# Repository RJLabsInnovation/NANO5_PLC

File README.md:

NANO5_PLC
===========
  Design and (C) 2021 RJLabs Innovation <rjlabs.innovation@gmail.com> 
  
  Provided under the terms of the CC0 1.0 Universal license.

Overview
--------
  This design board is based Outseal PLC V.5 [Outseal Website](http://www.outseal.com/web/produk). The main goal of this project to provide sigle side PCB that can be produce in house using transfer paper or negatif film method.

Key Feature
-------- 
* 2 Analog Input 0 - 20mA Or 0 -5V
* Built-in Modbus RTU
* Built-in external EEPROM 24CXX
* 8 Isolated Digital Input (12V - 24V)
* 2 Relay On Board with Surge Protection
* 6 Open Colector Digital Output
* Add On RTC DS3231 & Bluethoot HC05/06 

TODO
--------
* Add Regulator input power From LDO using Switching fore wide input voltage
* Add filter On input power stage
*

FINAL PRODUCT 3D RENDER
--------

Donations
--------
To support this project, you can make a donation to its current maintainer:

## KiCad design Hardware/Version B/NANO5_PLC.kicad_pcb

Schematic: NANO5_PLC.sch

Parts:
C1, C6, C9, C10, C11, C12, C13, C14, C15, C16, C17, C21, C22, C23: C_Small; C_Disc_D3.8mm_W2.6mm_P2.50mm
C5: 100u; CP_Radial_D5.0mm_P2.50mm
C7: 10n; C_0805_2012Metric_Pad1.15x1.40mm_HandSolder
C8, C25, C26, C27: 100n; C_0805_2012Metric
C28, C29: 22p; C_0805_2012Metric
D1: 1N4007; D_SMB
D2, D19: TS4148; D_0805_2012Metric
D3: 1N4007; D_1206_3216Metric
D4, D5, D6, D7, D8, D9, D10, D11, D14, D16, D18, D20: LED; LED_0805_2012Metric
D12: LED_ALT; LED_D3.0mm
D13: Grn; LED_0805_2012Metric_Pad1.15x1.40mm_HandSolder
D15, D17, D21: TS4148; D_1206_3216Metric
F1: Polyfuse_Small; Fuse_1206_3216Metric
FID1, FID2: Fiducial; Fiducial_1mm_Mask2mm
H1, H2, H3, H4: MountingHole; MountingHole_3.2mm_M3_DIN965_Pad
H5, H6, H7: MountingHole; mouse-bite-2mm-slot
J2, J3, J4, J5, J6, J16, J17, J18, J19, J20: Conn_01x03; TerminalBlock_bornier-3_P5.08mm
J7, J10: Conn_01x06; PinHeader_1x06_P2.54mm_Vertical
J8, J12, J21: Conn_01x02; PinHeader_1x02_P2.54mm_Vertical
J9: Conn_02x04_Odd_Even; PinSocket_2x04_P2.54mm_Vertical
J11: Debug; PinHeader_1x06_P2.54mm_Vertical
J13: Conn_01x05; PinHeader_1x05_P2.54mm_Vertical
J22: MP1584; SRT_MPT1584EN_Module
J23: Conn_01x04; JST_XH_B4B-XH-AM_1x04_P2.50mm_Vertical
J24: Conn_01x02; TerminalBlock_bornier-2_P5.08mm
J25: Conn_02x04_Odd_Even; PinSocket_2x04_P2.54mm_Horizontal
J26: Conn_02x04_Odd_Even; PinHeader_2x04_P2.54mm_Horizontal
K1, K2, K3, K4: SANYOU_SRD_Form_C; Relay_SPDT_SANYOU_SRD_Series_Form_C
Q1, Q2, Q3, Q4, Q5: 2SC1815; SC-59
R1, R2, R3: 1k; R_0805_2012Metric_Pad1.20x1.40mm_HandSolder
R4, R5, R6, R7, R8, R9, R10, R11, R12, R13, R20, R21, R22, R23, R24, R25, R26, R27, R28, R29, R30, R31: R; R_0805_2012Metric_Pad1.20x1.40mm_HandSolder
R14, R15, R16, R17: R_Small; R_0805_2012Metric
R18: 220; R_Axial_DIN0204_L3.6mm_D1.6mm_P5.08mm_Horizontal
R19: 1k; R_0805_2012Metric_Pad1.15x1.40mm_HandSolder
RV1, RV2, RV5, RV6: Varistor; RV_Disc_D12mm_W3.9mm_P7.5mm
RV3, RV4: R_POT; Potentiometer_Bourns_3299W_Vertical
SW1, SW2: SW_DIP_x02; SW_DIP_SPSTx02_Slide_Omron_A6S-210x_W8.9mm_P2.54mm
U2: SP3485EN; SOIC-8_3.9x4.9mm_P1.27mm
U3, U4, U5, U6, U7, U8, U9, U10: EL817; SSO-4_6.7x5.1mm_P2.54mm_Clearance8mm
U11: M24C01; SOIC-8_3.9x4.9mm_P1.27mm
U14: ATmega328-AU; TQFP-32_7x7mm_P0.8mm
U15: LM358; SOIC-8_3.9x4.9mm_P1.27mm
Y1: Crystal_Small; Crystal_SMD_HC49-SD

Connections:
2: U6.4
3: U5.4
4: U4.4
5: U3.4
+5V: C5.1, C6.1, C23.1, C26.1, C27.1, D1.1 (K), D2.1, D15.1, D17.1, D19.1, D21.1, J6.1, J7.5, J10.5, J21.2, J22.3, K1.2, K2.2, K3.2, K4.2, R1.1, R5.2, R21.2, R23.2, R26.2, R27.2, U2.8 (VCC), U11.8 (VCC), U14.4, U14.6, U14.18
/Vin: C17.1, D3.1 (K), J22.1
A: J6.3, U2.6 (A)
A0: U7.4, U14.23
A1: U8.4, U14.24
A2: U9.4, U14.25
A3: U10.4, U14.26
A4: J7.4, U11.5 (SDA), U14.27
A5: J7.3, U11.6 (SCL), U14.28
A6: C21.1, R16.1, U14.19
A7: C22.1, R17.1, U14.22
B: J6.2, U2.7 (B)
D2: U14.32
D3: U14.1
D4: U14.2
D5: U14.9
D6: R22.2, U14.10
D7: U14.11
D8: U14.12
D9: R28.2, U14.13
D10: U14.14
D11: R20.2, U14.15
D12: R24.2, U14.16
D13: R25.2, U14.17
GND: C5.2, C6.2, C7.2, C17.2, C21.2, C22.2, C23.2, C25.2, C26.2, C27.2, C28.2, C29.2, D13.1 (K), J5.1, J7.6, J10.4, J11.1, J18.1, J20.1, J20.2, J22.2, J22.4, Q1.1 (E), Q2.1 (E), Q3.1 (E), Q4.1 (E), Q5.1 (E), R14.2, R15.2, RV3.2, RV3.3, RV4.2, RV4.3, U2.4 (DI), U2.5 (GND), U3.3, U4.3, U5.3, U6.3, U7.3, U8.3, U9.3, U10.3, U11.1 (E0), U11.2 (E1), U11.3 (E2), U11.4 (VSS), U11.7 (~WC), U14.3, U14.5, U14.21
GNDA: C9.1, C10.1, C11.1, C12.1, C13.1, C14.1, C15.1, C16.1, J17.1, U3.2, U4.2, U5.2, U6.2, U7.2, U8.2, U9.2, U10.2
INA1: J18.2, R14.1, R16.2, SW2.4
INA2: J18.3, R15.1, R17.2, SW2.3
unnamed: C1.1, R28.1, R29.2, U15.3
unnamed: C1.2, R29.1, R30.1
unnamed: C8.1, J11.6
unnamed: C9.2, D4.1 (K), U3.1
unnamed: C10.2, D5.1 (K), U4.1
unnamed: C11.2, D6.1 (K), U5.1
unnamed: C12.2, D7.1 (K), U6.1
unnamed: C13.2, D8.1 (K), U7.1
unnamed: C14.2, D9.1 (K), U8.1
unnamed: C15.2, D10.1 (K), U9.1
unnamed: C16.2, D11.1 (K), U10.1
unnamed: C25.1, U14.20
unnamed: D2.2, J11.3
unnamed: D3.2 (A), F1.1
unnamed: D4.2 (A), R6.2
unnamed: D5.2 (A), R7.2
unnamed: D6.2 (A), R8.2
unnamed: D7.2 (A), R9.2
unnamed: D8.2 (A), R10.2
unnamed: D9.2 (A), R11.2
unnamed: D10.2 (A), R12.2
unnamed: D11.2 (A), R13.2
unnamed: D12.2 (A), R18.2
unnamed: D13.2 (A), R19.1
unnamed: D14.1 (K), D15.2, K3.5, Q2.2 (C)
unnamed: D14.2 (A), R21.1
unnamed: D16.1 (K), D17.2, K4.5, Q3.2 (C)
unnamed: D16.2 (A), R23.1
unnamed: D18.1 (K), D19.2, K2.5, Q4.2 (C)
unnamed: D18.2 (A), R26.1
unnamed: D20.1 (K), D21.2, K1.5, Q5.2 (C)
unnamed: D20.2 (A), R27.1
unnamed: J8.2, J10.2
unnamed: J8.1, J10.3
unnamed: J11.4, R3.1
unnamed: J11.5, R2.1
unnamed: K1.1, RV1.1
unnamed: K1.3, RV1.2
unnamed: K2.1, RV2.1
unnamed: K2.3, RV2.2
unnamed: K3.1, RV5.1
unnamed: K3.3, RV5.2
unnamed: K4.1, RV6.1
unnamed: K4.3, RV6.2
unnamed: Q1.2 (C), R5.1, U2.2 (~RE~), U2.3 (DE)
unnamed: Q1.3 (B), R4.1
unnamed: Q2.3 (B), R20.1
unnamed: Q3.3 (B), R22.1
unnamed: Q4.3 (B), R24.1
unnamed: Q5.3 (B), R25.1
unnamed: R30.2, R31.1, U15.6
unnamed: R31.2, U15.7
unnamed: RV3.1, SW2.1
unnamed: RV4.1, SW2.2
unnamed: U15.1, U15.2, U15.5
OR1: J4.1
OR2: J4.2
OR3: J5.3
OR4: J5.2
RESET: C7.1, C8.2, R1.2, U14.29
RL3: J4.3
RL4: J3.1
RL5: J3.2
RL6: J3.3
RL7: J2.1
RL8: J2.2
RX: J12.1, R3.2, U14.30
RX1: J12.2, U2.1 (RO)
S1: J17.2, R10.1
S2: J17.3, R11.1
S3: J19.1, R12.1
S4: J19.2, R13.1
S5: J19.3, R9.1
S6: J16.1, R8.1
S7: J16.2, R7.1
S8: J16.3, R6.1
TX: R2.2, R4.2, U14.31
V: F1.2, J20.3
VRL: J2.3, J21.1
X1: C28.1, U14.7, Y1.1
X2: C29.1, U14.8, Y1.2

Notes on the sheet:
D13 = R1 D12 = R2 D11 = R3 D10 = R8 D9 = R7 D8 = R6 D7 = R5 D6 = R4 D5 = S8* D4 = S7* D3 = S6* D2 = S5* A0 = S1* A1 = S2* A2 = S3* A3 = S4* A4 = SDA A5 = SCL A6 = A1 A7 = A2
INPUT STAGE
OUTPUT STAGE
REGULATOR CIRCUIT
NANO5 PLC OUTSEAL V5 COMPETIBLE
COPYRIGHT RJLabs Innovation @2021 E-mail : rjlabs.innovation@gmail.com

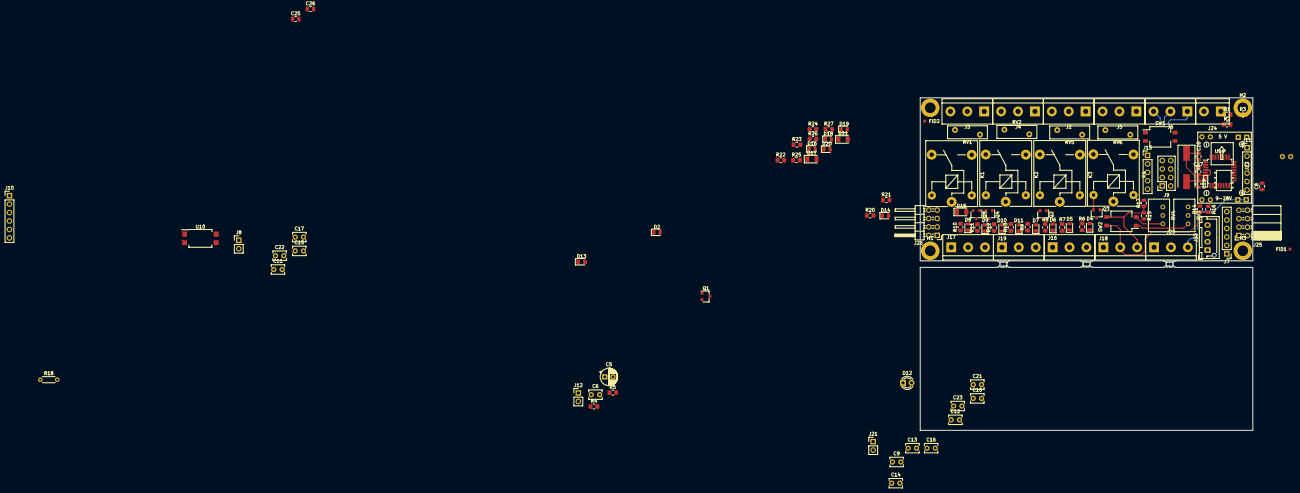
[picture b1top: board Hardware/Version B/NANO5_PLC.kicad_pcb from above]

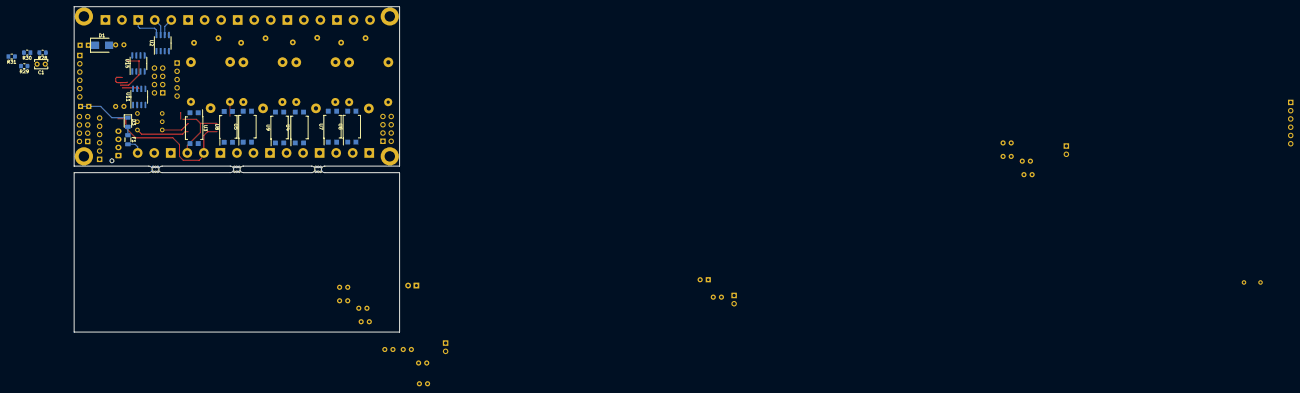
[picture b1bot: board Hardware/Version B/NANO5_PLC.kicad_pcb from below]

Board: 4 copper layers, 100.0 x 100.0 mm, 135 parts (18 on the bottom side), 91 nets.

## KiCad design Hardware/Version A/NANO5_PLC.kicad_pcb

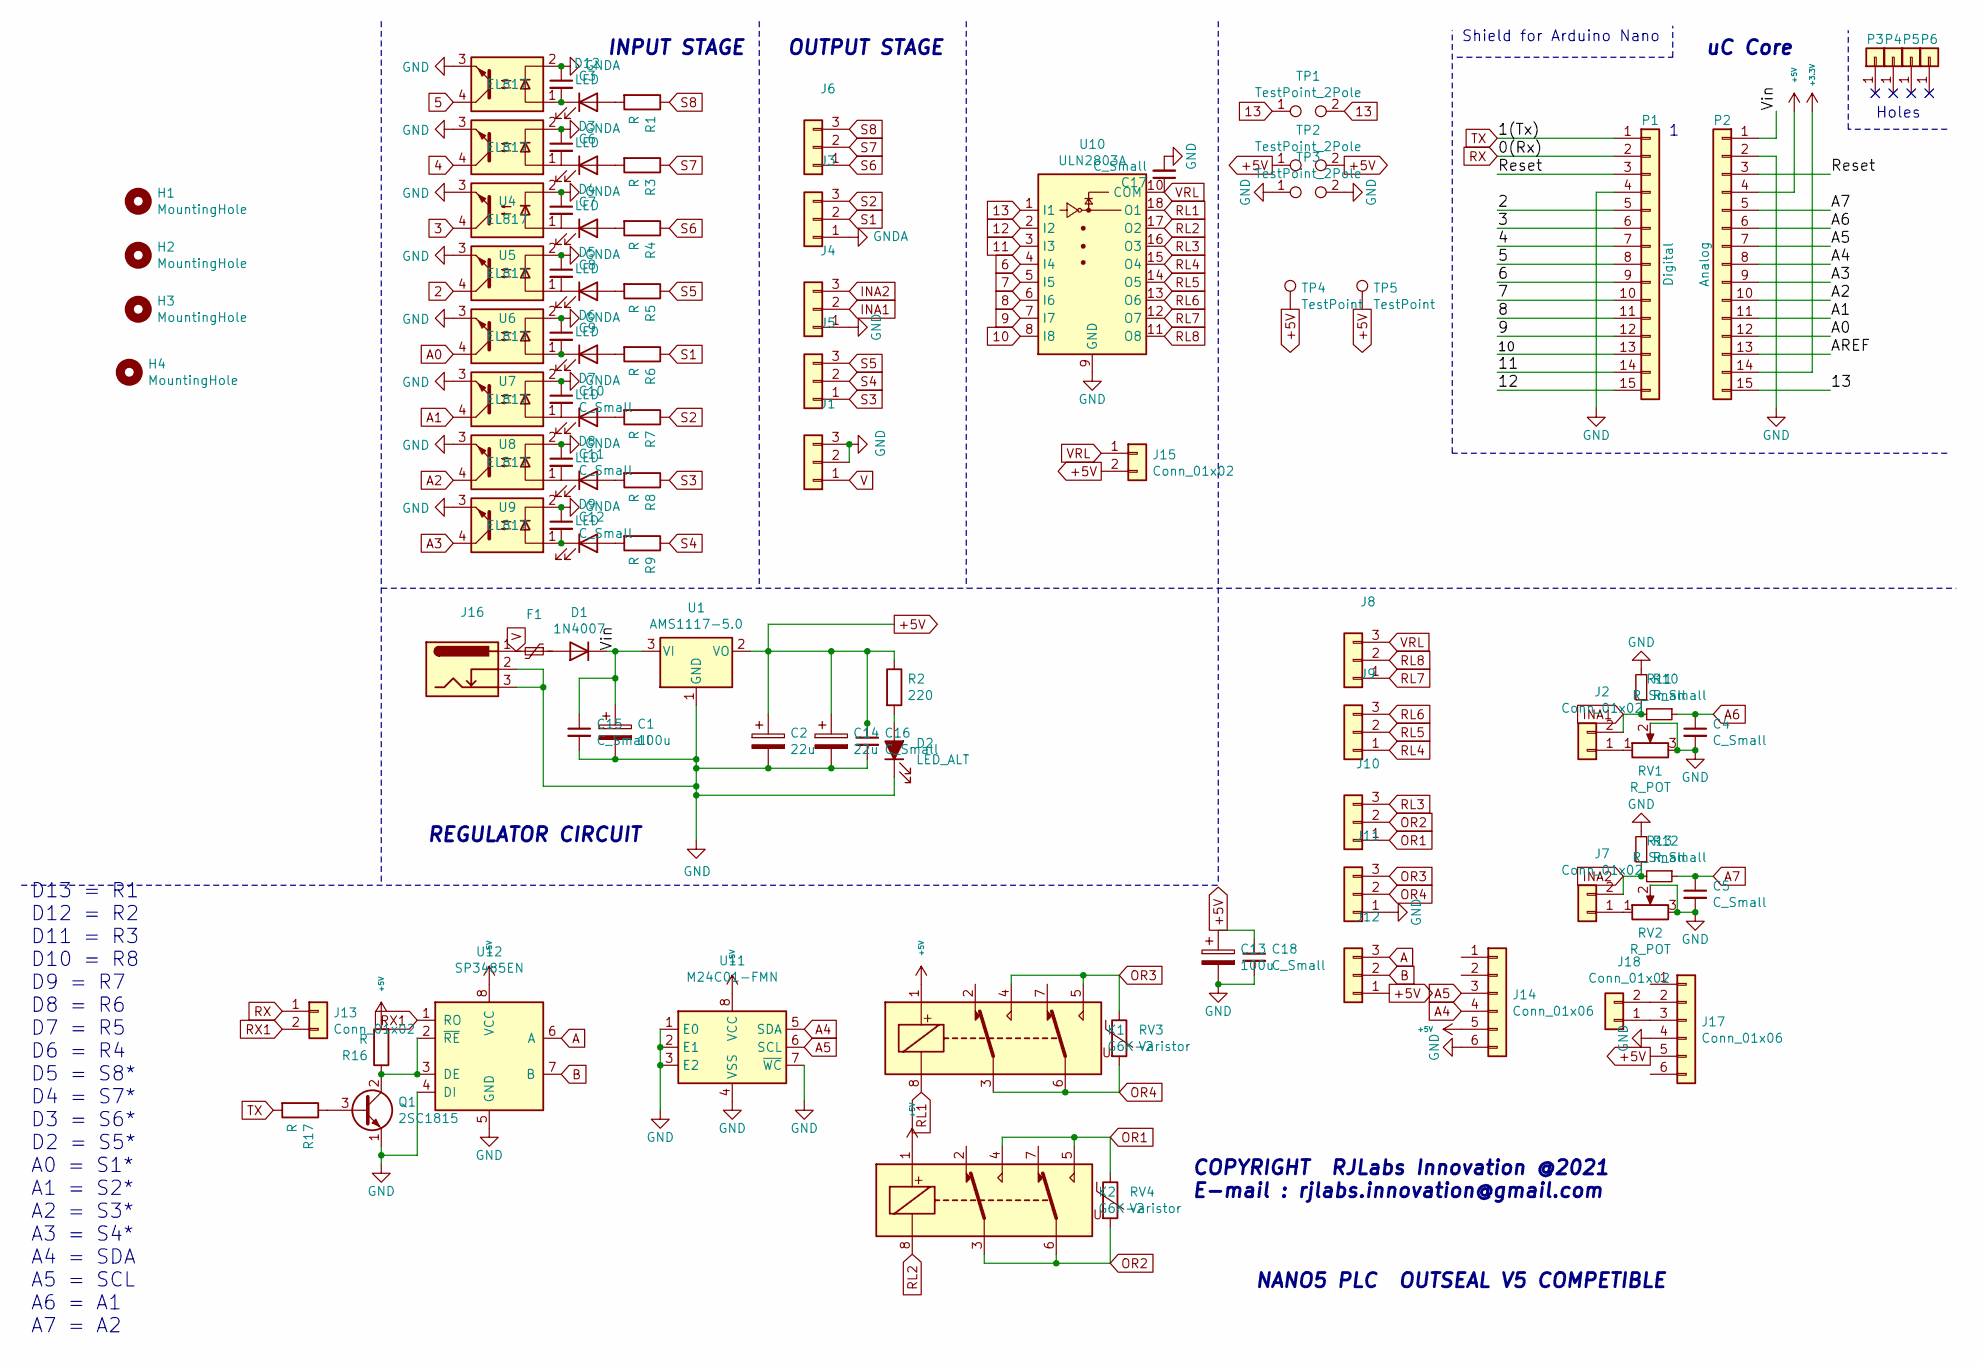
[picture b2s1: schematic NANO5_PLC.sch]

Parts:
C1, C13: 100u; CP_Radial_D5.0mm_P2.50mm
C2, C14: 22u; CP_Radial_D5.0mm_P2.50mm
C3, C4, C5, C6, C7, C8, C9, C10, C11, C12, C15, C16, C17, C18: C_Small; C_Disc_D3.8mm_W2.6mm_P2.50mm
D1: 1N4007; D_A-405_P2.54mm_Vertical_KathodeUp
D2: LED_ALT; LED_D3.0mm
D3, D4, D5, D6, D7, D8, D9, D12: LED; LED_D3.0mm
F1: Polyfuse_Small; Fuse_BelFuse_0ZRE0033FF_L11.4mm_W3.8mm
H1, H2, H3, H4: MountingHole; MountingHole_3.2mm_M3_DIN965_Pad
J1, J3, J4, J5, J6, J8, J9, J10, J11, J12: Conn_01x03; TerminalBlock_Phoenix_MKDS-1,5-3-5.08_1x03_P5.08mm_Horizont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
J2, J7, J13, J15, J18: Conn_01x02; PinHeader_1x02_P2.54mm_Vertical
J14, J17: Conn_01x06; PinHeader_1x06_P2.54mm_Vertical
J16: Barrel_Jack_Switch_Pin3Ring; BarrelJack_Horizontal
K1, K2: G6K-2; Relay_DPDT_Omron_G5V-2
P1: Digital; Socket_Strip_Arduino_1x15
P2: Analog; Socket_Strip_Arduino_1x15
P3, P4, P5, P6: CONN_01X01; 1pin_Nano
Q1: 2SC1815; TO-92_Inline_Wide
R1, R3, R4, R5, R6, R7, R8, R9, R16, R17: R; R_0805_2012Metric_Pad1.20x1.40mm_HandSolder
R2: 220; R_Axial_DIN0204_L3.6mm_D1.6mm_P5.08mm_Horizontal
R10, R11, R12, R13: R_Small; R_Axial_DIN0204_L3.6mm_D1.6mm_P5.08mm_Horizontal
RV1, RV2: R_POT; Potentiometer_Bourns_3299W_Vertical
RV3, RV4: Varistor; RV_Disc_D12mm_W3.9mm_P7.5mm
TP1: TestPoint_2Pole; TestPoint_Bridge_Pitch7.62mm_Drill1.3mm
TP2: TestPoint_2Pole; TestPoint_Bridge_Pitch6.35mm_Drill1.3mm
TP3: TestPoint_2Pole; TestPoint_Bridge_Pitch5.08mm_Drill1.3mm
TP4, TP5: TestPoint; TestPoint_Loop_D1.80mm_Drill1.0mm_Beaded
U1: AMS1117-5.0; SOT-223-3_TabPin2
U2, U3, U4, U5, U6, U7, U8, U9: EL817; DIP-4_W7.62mm
U10: ULN2803A; SOIC-18W_7.5x11.6mm_P1.27mm
U11: M24C01-FMN; SOIC-8_3.9x4.9mm_P1.27mm
U12: SP3485EN; SOIC-8_3.9x4.9mm_P1.27mm

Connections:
2: P1.5, U5.4
3: P1.6, U4.4
4: P1.7, U3.4
5: P1.8, U2.4
6: P1.9, U10.4 (I4)
7: P1.10, U10.5 (I5)
8: P1.11, U10.6 (I6)
9: P1.12, U10.7 (I7)
10: P1.13, U10.8 (I8)
11: P1.14, U10.3 (I3)
12: P1.15, U10.2 (I2)
13: P2.15, TP1.1, TP1.2, U10.1 (I1)
+3V3: P2.14
+5V: C2.1, C13.1, C14.1, C16.1, C18.1, J12.1, J14.5, J15.2, J17.5, K1.1, K2.1, P2.4, R2.1, R16.2, TP2.1, TP2.2, TP4.1, TP5.1, U1.2 (VO), U11.8 (VCC), U12.8 (VCC)
/AREF: P2.13
/Reset: P1.3, P2.3
/Vin: C1.1, C15.1, D1.1 (K), P2.1, U1.3 (VI)
A: J12.3, U12.6 (A)
A0: P2.12, U6.4
A1: P2.11, U7.4
A2: P2.10, U8.4
A3: P2.9, U9.4
A4: J14.4, P2.8, U11.5 (SDA)
A5: J14.3, P2.7, U11.6 (SCL)
A6: C4.1, P2.6, R11.1
A7: C5.1, P2.5, R13.1
B: J12.2, U12.7 (B)
GND: C1.2, C2.2, C4.2, C5.2, C13.2, C14.2, C15.2, C16.2, C17.2, C18.2, D2.1 (K), J1.2, J1.3, J4.1, J11.1, J14.6, J16.2, J16.3, J17.4, P1.4, P2.2, Q1.1 (E), R10.2, R12.2, RV1.2, RV1.3, RV2.2, RV2.3, TP3.1, TP3.2, U1.1 (GND), U2.3, U3.3, U4.3, U5.3, U6.3, U7.3, U8.3, U9.3, U10.9 (GND), U11.1 (E0), U11.2 (E1), U11.3 (E2), U11.4 (VSS), U11.7 (~WC), U12.4 (DI), U12.5 (GND)
GNDA: C3.1, C6.1, C7.1, C8.1, C9.1, C10.1, C11.1, C12.1, J3.1, U2.2, U3.2, U4.2, U5.2, U6.2, U7.2, U8.2, U9.2
INA1: J2.2, J4.2, R10.1, R11.2
INA2: J4.3, J7.2, R12.1, R13.2
unnamed: C3.2, D12.1 (K), U2.1
unnamed: C6.2, D3.1 (K), U3.1
unnamed: C7.2, D4.1 (K), U4.1
unnamed: C8.2, D5.1 (K), U5.1
unnamed: C9.2, D6.1 (K), U6.1
unnamed: C10.2, D7.1 (K), U7.1
unnamed: C11.2, D8.1 (K), U8.1
unnamed: C12.2, D9.1 (K), U9.1
unnamed: D1.2 (A), F1.1
unnamed: D2.2 (A), R2.2
unnamed: D3.2 (A), R3.2
unnamed: D4.2 (A), R4.2
unnamed: D5.2 (A), R5.2
unnamed: D6.2 (A), R6.2
unnamed: D7.2 (A), R7.2
unnamed: D8.2 (A), R8.2
unnamed: D9.2 (A), R9.2
unnamed: D12.2 (A), R1.2
unnamed: J2.1, RV1.1
unnamed: J7.1, RV2.1
unnamed: J17.2, J18.2
unnamed: J17.3, J18.1
unnamed: Q1.2 (C), R16.1, U12.2 (~RE~), U12.3 (DE)
unnamed: Q1.3 (B), R17.1
OR1: J10.1, K2.4, K2.5, RV4.1
OR2: J10.2, K2.3, K2.6, RV4.2
OR3: J11.3, K1.4, K1.5, RV3.1
OR4: J11.2, K1.3, K1.6, RV3.2
RL1: K1.8, U10.18 (O1)
RL2: K2.8, U10.17 (O2)
RL3: J10.3, U10.16 (O3)
RL4: J9.1, U10.15 (O4)
RL5: J9.2, U10.14 (O5)
RL6: J9.3, U10.13 (O6)
RL7: J8.1, U10.12 (O7)
RL8: J8.2, U10.11 (O8)
RX: J13.1, P1.2
RX1: J13.2, U12.1 (RO)
S1: J3.2, R6.1
S2: J3.3, R7.1
S3: J5.1, R8.1
S4: J5.2, R9.1
S5: J5.3, R5.1
S6: J6.1, R4.1
S7: J6.2, R3.1
S8: J6.3, R1.1
TX: P1.1, R17.2
V: F1.2, J1.1, J16.1
VRL: C17.1, J8.3, J15.1, U10.10 (COM)

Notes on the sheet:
Holes
Shield for Arduino Nano
D13 = R1 D12 = R2 D11 = R3 D10 = R8 D9 = R7 D8 = R6 D7 = R5 D6 = R4 D5 = S8* D4 = S7* D3 = S6* D2 = S5* A0 = S1* A1 = S2* A2 = S3* A3 = S4* A4 = SDA A5 = SCL A6 = A1 A7 = A2
INPUT STAGE
OUTPUT STAGE
REGULATOR CIRCUIT
NANO5 PLC OUTSEAL V5 COMPETIBLE
COPYRIGHT RJLabs Innovation @2021 E-mail : rjlabs.innovation@gmail.com
uC Core

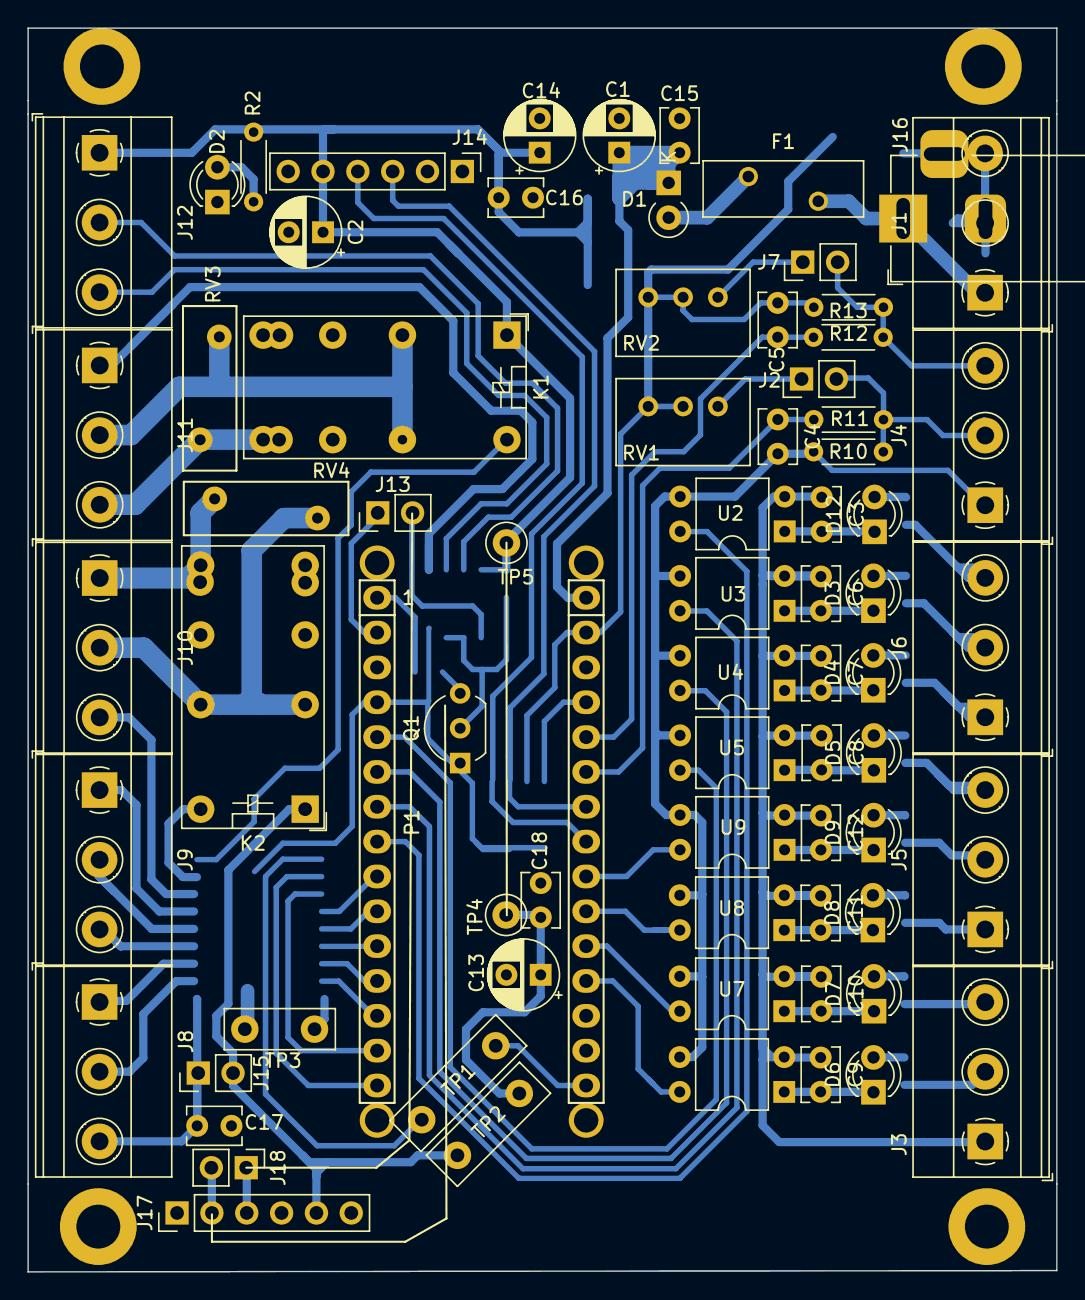
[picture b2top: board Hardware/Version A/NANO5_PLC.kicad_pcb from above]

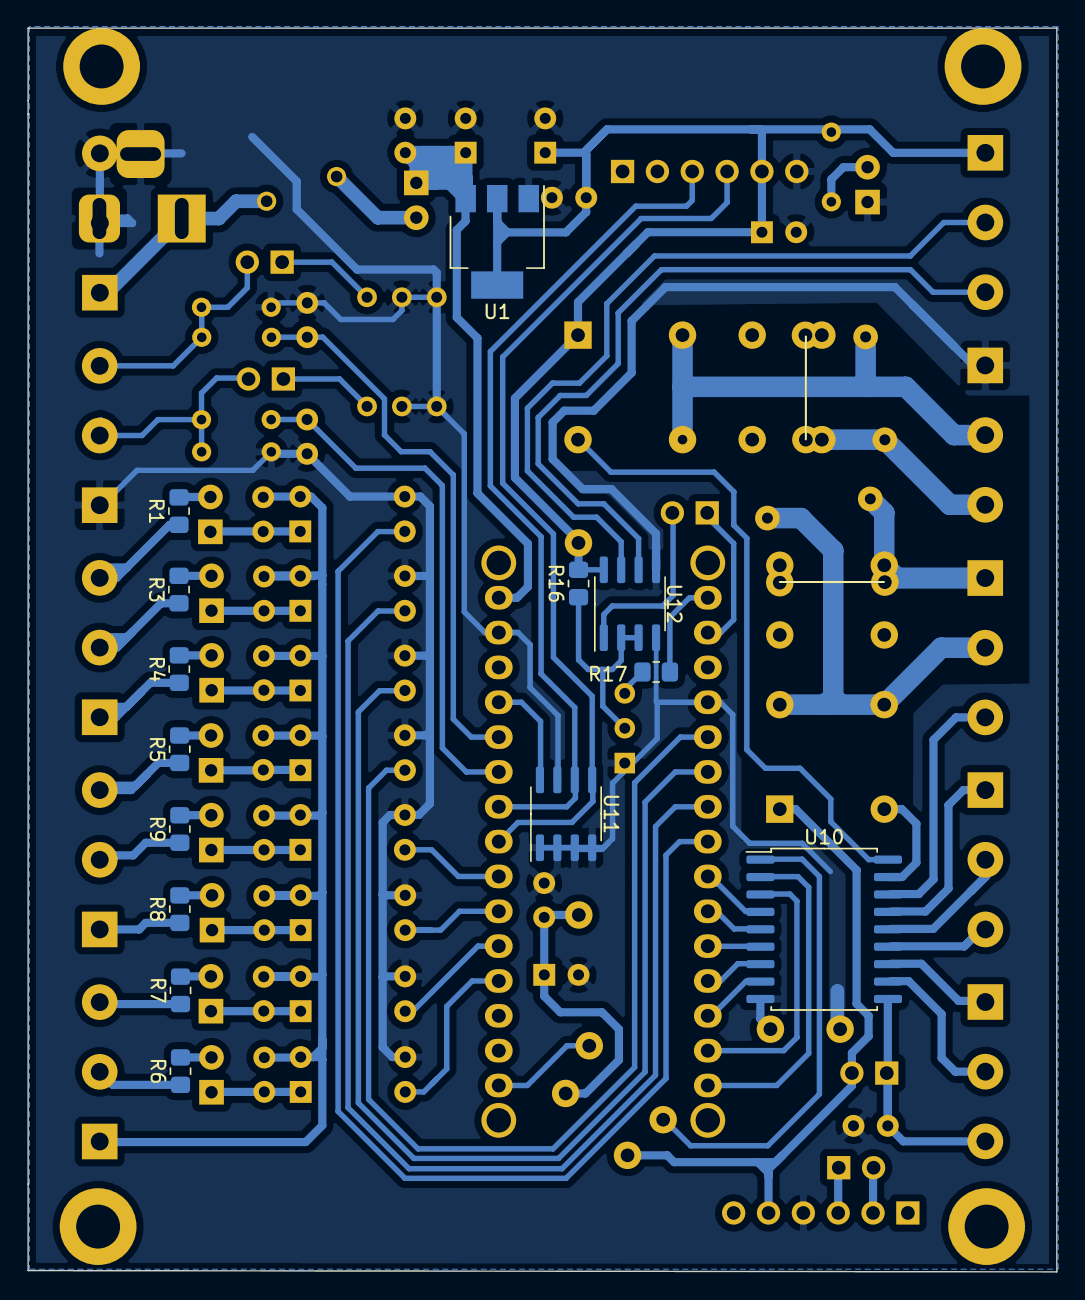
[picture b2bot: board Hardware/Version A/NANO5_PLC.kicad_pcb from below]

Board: 2 copper layers, 75.0 x 90.7 mm, 96 parts (14 on the bottom side), 78 nets.

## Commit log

2021-08-08 update image render 3d final product
2021-08-08 minor update
2021-08-08 fix gitignore
2021-08-08 update manual schematic pdf
2021-08-08 update firmware
2021-08-08 update firware
2021-08-08 Update Production File
2021-08-09 Update donate link
2021-11-06 update smd version
